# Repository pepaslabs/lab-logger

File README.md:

# lab-logger
A USB-based temperature / humidity logger, based on a Si7021 breakout board.

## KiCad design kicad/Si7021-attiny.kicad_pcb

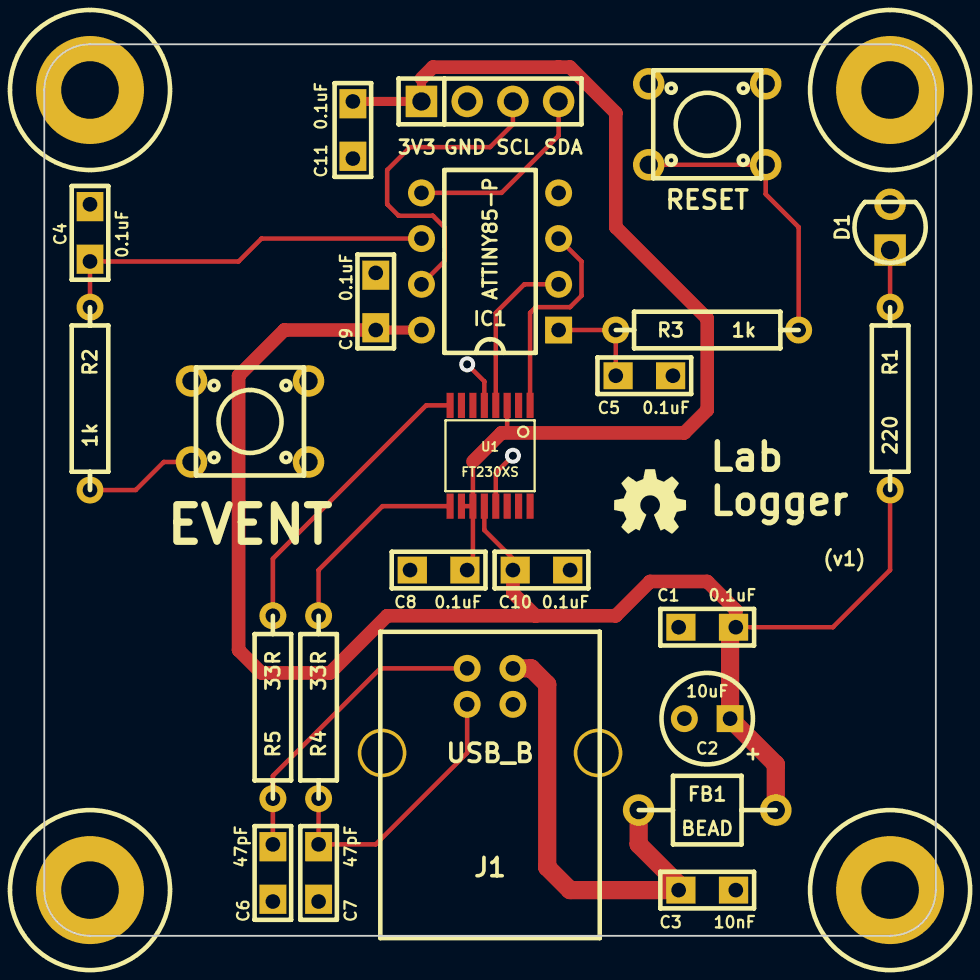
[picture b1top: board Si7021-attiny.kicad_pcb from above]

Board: 2 copper layers, 49.5 x 49.5 mm, 28 parts (0 on the bottom side), 17 nets.

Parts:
C1, C4, C5, C8, C9, C10, C11: 0.1uF; CERCAP_15_059B_0805
C2: 10uF; ELCAP_10_20_V_059A
C3: 10nF; CERCAP_15_059B_0805
C6, C7: 47pF; CERCAP_15_059B_0805
D1: LED; LED_3MM_069A
EVENT: EVENT; 1825910-6
FB1: BEAD; FERRITE_AXIAL_03_069A
H***: Val**; hole_M3
H***#2, H***#3, H***#4: Val**; hole_M3
IC1: ATTINY85-P; DIP8_059A_PL
J1: USB_B
R1: 220; R_AXIAL_0W25_059A_PL
R2, R3: 1k; R_AXIAL_0W25_059A_PL
R4, R5: 33R; R_AXIAL_0W25_059A_PL
RESET: RESET; 1825910-6
U1: FT230XS; SSOP-16
U2: SI7021-BREAKOUT; SIL-4

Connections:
3V3: C8.1, C11.1, U1.3, U1.10, U1.11, U2.1
5V: C1.1, C2.1, C9.1, C10.1, FB1.2, IC1.8, R1.2, U1.12
GND: C1.2, C2.2, C3.2, C4.2, C5.2, C6.2, C7.2, C8.2, C9.2, C10.2, C11.2, D1.2, EVENT.2, IC1.4, J1.4, J1.5, J1.6, RESET.2, U1.5, U1.13, U2.2
unnamed: R4.2, U1.9
unnamed: R5.2, U1.8
unnamed: D1.1, R1.1
unnamed: C7.1, J1.3, R4.1
unnamed: C4.1, IC1.6, R2.1
unnamed: C5.1, IC1.1, R3.1
unnamed: EVENT.1, R2.2
unnamed: R3.2, RESET.1
unnamed: C3.1, FB1.1, J1.1
unnamed: C6.1, J1.2, R5.1
RX: IC1.2, U1.4
SCL: IC1.7, U2.3
SDA: IC1.5, U2.4
TX: IC1.3, U1.1

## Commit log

2017-07-02 Initial release
2022-07-27 use correct arduino folder name
